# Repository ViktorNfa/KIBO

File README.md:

# KIBO Robot

## Overview

KIBO is an advanced robotics platform designed for modularity and versatility. The project includes hardware designs, electronics, and firmware to control a multi-legged wheeled robotic system. The primary goal is to implement inverse kinematics (IK) walking modes and wheeled modes and gait optimization using Model Predictive Path Integral (MPPI) control through micro-ROS (uROS) in ESP32 and ROS2 nodes with C++.

## Table of Contents

1. [Getting Started](#getting-started)
2. [Features](#features)
3. [Hardware Overview](#hardware-overview)
   - [CAD Files](#cad-files)
   - [Electronics](#electronics)
4. [Software Overview](#software-overview)
   - [ESP32 Firmware](#esp32-firmware)
   - [ROS2 Nodes](#ros2-nodes)
   - [Gait Optimization with MPPI](#gait-optimization-with-mppi)
5. [Installation and Setup](#installation-and-setup)
6. [Usage](#usage)
7. [Contributing](#contributing)
8. [License](#license)
9. [Acknowledgments](#acknowledgments)

## Getting Started

This project is intended for researchers, hobbyists, and developers interested in robotics. To get started with KIBO:

1. Clone this repository.
2. Set up the hardware following the instructions in the [Hardware Overview](#hardware-overview) section.
3. Flash the ESP32 with the firmware provided in the [ESP32 Firmware](#esp32-firmware) section.
4. Configure and run the ROS2 nodes as described in the [ROS2 Nodes](#ros2-nodes) section.

## Features

- **Inverse Kinematics (IK) Walking Modes**: Implement various walking gaits using IK.
- **Gait Optimization**: Optimize the robot's gait using Model Predictive Path Integral (MPPI) control.
- **Micro-ROS (uROS) Integration**: Utilize uROS for real-time communication between ESP32 and ROS2 nodes.
- **ESP32-based Control**: Leverage the ESP32 microcontroller for low-level control and sensor integration.

## Hardware Overview

### CAD Files

The `CAD` directory contains the STL files required to 3D print the robot's structural components. These include parts like the body frame, limbs, and armor:

- **Body Frame**: `Kibo frame.stl`, `Frame End Tip.stl`,`L298N Driver Spacer.stl`
- **Coxa Components**: `Coxa Left.stl`, `Coxa Right.stl`
- **Femur Components**:`Femur Right.stl`,`Femur Left.stl`
- **Tibia Components**: `Tibia.stl`, `Tibia Slider.stl`
- **Armor**: `Bottom Body Armor Left.stl`, `Bottom Body Armor Right.stl`, `Body Armor Spoiler.stl`, `Top Body Armor.stl`
- **Miscellaneous**: `Servo Back Plate.stl`, `Servo Bushing.stl`, `ring.stl`, `Battery holder.stl`

These components can be printed using any standard 3D printer. Ensure that you use durable materials like PLA+ or PETG for better structural integrity.

### Electronics

The `Electronics` directory contains the KiCad files for the KIBO V1 PCB, including:

- **Schematic**: `KIBO V1.kicad_sch`
- **PCB Layout**: `KIBO V1.kicad_pcb`
- **Manufacturing Files**: `KIBO_PCBFab.zip`

You can manufacture the PCB using the provided Gerber files or modify the design using KiCad.

#### Symbols and Footprints

This subdirectory includes additional component libraries for symbols and footprints used in the PCB design:

- ESP32-CAM
- GY-521 (IMU Sensor)
- HC-SR04 (Ultrasonic Sensor)

## Software Overview

### ESP32 Firmware

The ESP32 firmware is still to be developed, but test files can be located in the `Firmware/esp32_tests` directory for the ESP32 and the `Firmware/esp32_cam_tests` directory for the ESP32-CAM. This firmware is responsible for:

- Starting FreeRTOS and seting up the tasks and priorities.
- Managing sensors and actuators.
- Communicating with ROS2 nodes via micro-ROS (uROS).

#### Key Files:

- `platformio.ini`: Configuration file for PlatformIO.
- `src/main.cpp`: Main entry point for the ESP32 application.
- `include/camera_pins.h`: Header files, e.g., defining the camera's GPIO pins.

### ROS2 Nodes

The ROS2 nodes are designed to handle higher-level control and coordination. These nodes communicate with the ESP32 using uROS and handle tasks such as:

- High-level motion planning.
- Real-time data processing from the robot's sensors.
- Gait optimization using MPPI.

#### Planned Features:

The following planned features will be added to the `Simulation` directory.

- **Inverse Kinematics (IK) Implementation**: Calculate joint angles for desired end-effector positions.
- **Gait Optimization with MPPI**: Optimize walking gaits to enhance stability and energy efficiency.

### Gait Optimization with MPPI

MPPI (Model Predictive Path Integral) control is a powerful method for optimizing the robot's gait. It will be used to predict and adjust the robot's movements in real-time, ensuring smooth and stable walking patterns.

## Installation and Setup

### Prerequisites

- **PlatformIO**: Required for building and flashing the ESP32 firmware.
- **ROS2 Humble**: Recommended version of ROS2 for running the ROS2 nodes.
- **uROS Agent**: Necessary for communication between ESP32 and ROS2.

### Instructions

1. **ESP32 Firmware**:
   - Navigate to the `Firmware/esp32_tests` directory.
   - Install the necessary PlatformIO dependencies.
   - Build and upload the firmware to your ESP32 module.

2. **ROS2 Nodes**:
   - Set up a ROS2 workspace and clone this repository into the `src` directory.
   - Build the workspace using `colcon build`.
   - Launch the nodes using the provided launch files.

## Usage

1. Power on the KIBO robot.
2. Launch the ROS2 nodes on your PC.
3. The ESP32 will automatically start communicating with the ROS2 nodes.
4. Use the provided ROS2 interfaces to command the robot and monitor its state.

## Contributing

We welcome contributions to the KIBO project! If you have suggestions, bug reports, or want to contribute new features, please open an issue or submit a pull request.

### Guidelines

- Follow the existing coding style.
- Document your code thoroughly.
- Test your contributions before submitting.

## License

This project is licensed under the MIT License - see the [LICENSE](LICENSE) file for details.

## Acknowledgments

We would like to thank the open-source community for their valuable tools and libraries that made this project possible.

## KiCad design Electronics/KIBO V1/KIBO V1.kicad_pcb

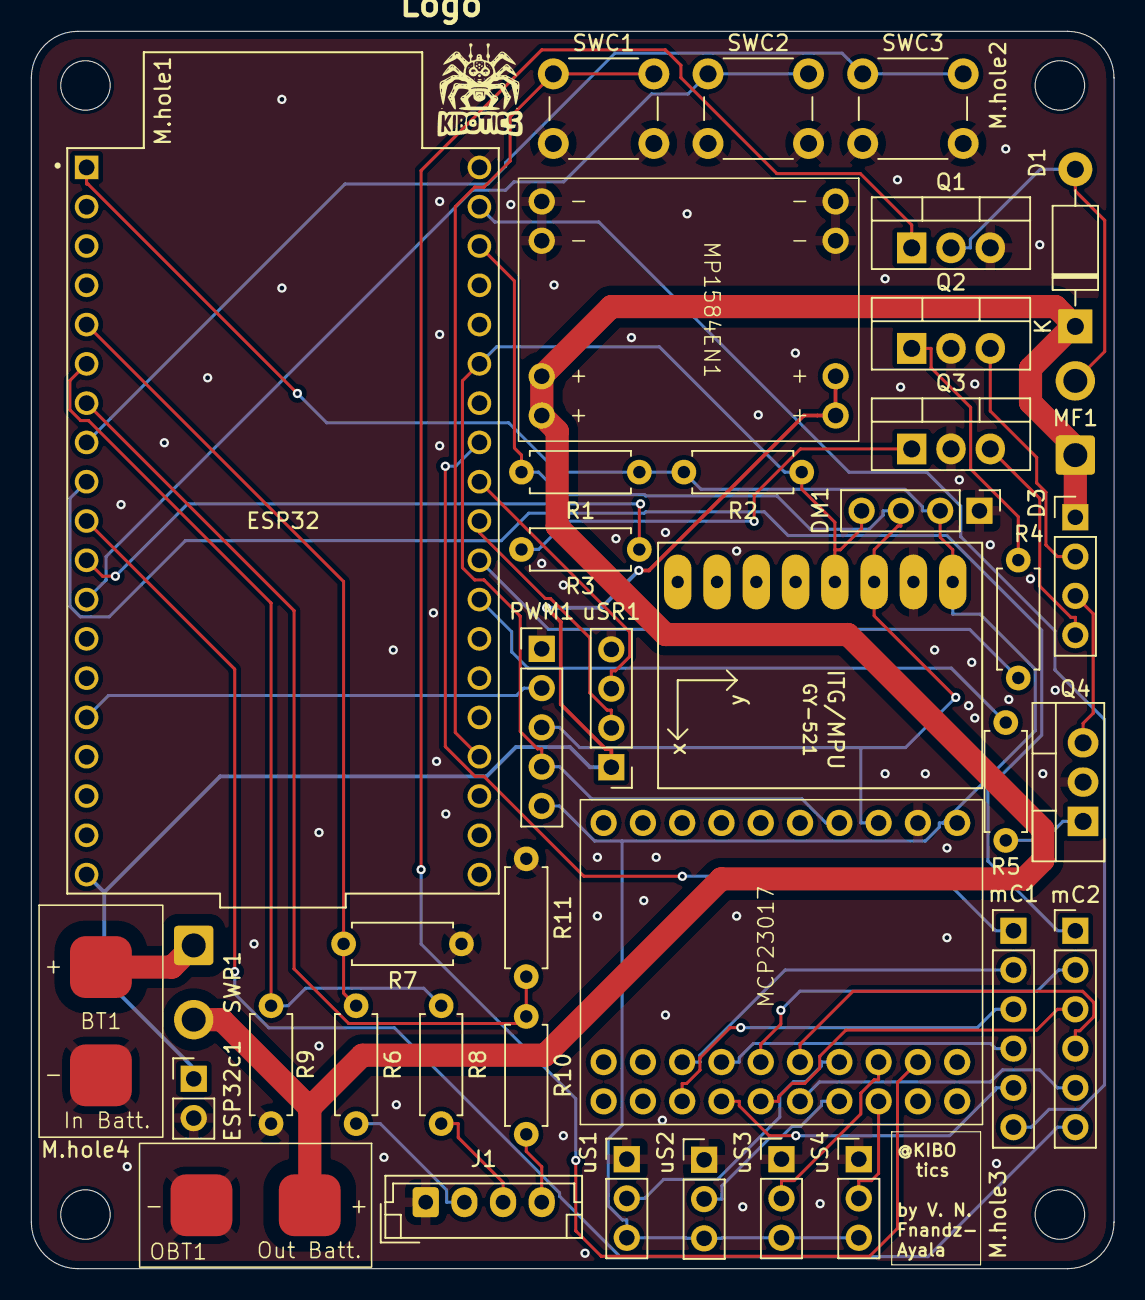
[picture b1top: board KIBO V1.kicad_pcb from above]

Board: 2 copper layers, 70.0 x 80.0 mm, 44 parts (0 on the bottom side), 46 nets.

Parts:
BT1: 11V1; 2xBatterty_Wire_Pads
D1: 1N4001; D_DO-41_SOD81_P10.16mm_Horizontal
D3: LED_AGRB; PinHeader_1x04_P2.54mm_Vertical
DM1: DM-OLED; PinHeader_1x04_P2.54mm_Vertical
ESP32: ESP32-DEVKITC; MODULE_ESP32-DEVKITC
ESP32c1: ESP32-CAM; PinHeader_1x02_P2.54mm_Vertical
GY-521: GY-521
J1: Conn_01x04; JST_EH_B4B-EH-A_1x04_P2.50mm_Vertical
Logo: LOGO
M.hole1, M.hole2, M.hole3, M.hole4: MountingHole_3.2mm_M3
MCP23017: PortExt; MCP23017
MF1: Fan; SolderWire-0.75sqmm_1x02_P4.8mm_D1.25mm_OD2.3mm
MP1584EN1: VoltConv; MP-1584EN
OBT1: UBEC; 2xBatterty_Wire_Pads
PWM1: PWM; PinHeader_1x05_P2.54mm_Vertical
Q1, Q2, Q3, Q4: TIP120; TO-220-3_Vertical
R1, R2: 4k7; R_Axial_DIN0207_L6.3mm_D2.5mm_P7.62mm_Horizontal
R3, R4, R5, R8: 1k; R_Axial_DIN0207_L6.3mm_D2.5mm_P7.62mm_Horizontal
R6, R10: 5k6; R_Axial_DIN0207_L6.3mm_D2.5mm_P7.62mm_Horizontal
R7: 22k; R_Axial_DIN0207_L6.3mm_D2.5mm_P7.62mm_Horizontal
R9: 680; R_Axial_DIN0207_L6.3mm_D2.5mm_P7.62mm_Horizontal
R11: 2k; R_Axial_DIN0207_L6.3mm_D2.5mm_P7.62mm_Horizontal
SWC1, SWC2, SWC3: SW_Push; SW_PUSH_6mm
SWP1: SWP; SolderWire-0.75sqmm_1x02_P4.8mm_D1.25mm_OD2.3mm
mC1, mC2: MotorDriver; PinHeader_1x06_P2.54mm_Vertical
uS1, uS2, uS3, uS4: uSwitch; PinHeader_1x03_P2.54mm_Vertical
uSR1: HC-SR04; PinHeader_1x04_P2.54mm_Vertical

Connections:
+3V3: DM1.2 (VCC_IN), ESP32.1 (3V3), GY-521.VCC, MCP23017.10 (VCC), PWM1.5 (VCC), R1.1, R2.1, uS1.3 (NO), uS2.3 (NO), uS3.3 (NO), uS4.3 (NO)
+5V: ESP32.19 (EXT_5V), ESP32c1.1 (5V), MP1584EN1.7 (OUT+), MP1584EN1.8 (OUT+), uSR1.1 (VCC)
+11V1: D1.1 (K), D3.1 (A), MF1.1 (+), MP1584EN1.3 (IN+), MP1584EN1.4 (IN+), OBT1.1 (IN+), SWP1.2 (B)
/B: ESP32.11 (IO27), R3.1
/CLL1: ESP32.5 (IO34), R6.1, R7.2
/CLL2: ESP32.6 (IO35), R8.1, R9.2
/CLL3: ESP32.7 (IO32), R10.1, R11.2
/ECHO: ESP32.30 (IO18), uSR1.3 (ECHO)
/FAN: MCP23017.27 (B6), Q1.1 (B)
/G: ESP32.28 (IO17), R4.1
/M1EN: ESP32.31 (IO19), mC1.1 (ENA)
/M1IN1: MCP23017.15 (B0), mC1.2 (IN1)
/M1IN2: MCP23017.16 (A0), mC1.3 (IN2)
/M2EN: ESP32.37 (IO23), mC1.6 (ENB)
/M2IN1: MCP23017.17 (B1), mC1.4 (IN3)
/M2IN2: MCP23017.18 (A1), mC1.5 (IN4)
/M3EN: ESP32.9 (IO25), mC2.1 (ENA)
/M3IN1: MCP23017.19 (B2), mC2.2 (IN1)
/M3IN2: MCP23017.20 (A2), mC2.3 (IN2)
/M4EN: ESP32.10 (IO26), mC2.6 (ENB)
/M4IN1: MCP23017.21 (B3), mC2.4 (IN3)
/M4IN2: MCP23017.22 (A3), mC2.5 (IN4)
/OE: ESP32.15 (IO13), PWM1.2 (OE)
/R: ESP32.27 (IO16), R5.1
/S1: MCP23017.23 (B4), uS1.2 (COM)
/S2: MCP23017.24 (A4), uS2.2 (COM)
/S3: MCP23017.25 (B5), uS3.2 (COM)
/S4: MCP23017.26 (A5), uS4.2 (COM)
/SCL: DM1.3 (SCL), ESP32.36 (IO22), GY-521.SCL, MCP23017.8 (SCK), PWM1.3 (SCL), R1.2
/SDA: DM1.4 (SDA), ESP32.33 (IO21), GY-521.SDA, MCP23017.7 (SDA), PWM1.4 (SDA), R2.2
/SW1: ESP32.23 (IO15), SWC1.1
/SW2: ESP32.12 (IO14), SWC2.1
/SW3: ESP32.8 (IO33), SWC3.1
/TRIG: ESP32.29 (IO5), uSR1.2 (TRIG)
GND: BT1.2 (-), DM1.1 (GND), ESP32.38 (GND3), ESP32c1.2 (GND@3), GY-521.GND, J1.1, MCP23017.9 (GND), MP1584EN1.1 (IN-), MP1584EN1.2 (IN-), MP1584EN1.5 (OUT-), MP1584EN1.6 (OUT-), OBT1.2 (IN-), PWM1.1 (GND), Q1.3 (E), Q2.2 (C), Q3.2 (C), Q4.2 (C), R7.1, R9.1, R11.1, SWC1.2, SWC2.2, SWC3.2, uS1.1 (NC), uS2.1 (NC), uS3.1 (NC), uS4.1 (NC), uSR1.4 (GND)
unnamed: BT1.1 (+), SWP1.1 (A)
unnamed: D1.2 (A), MF1.2 (-), Q1.2 (C)
unnamed: D3.4 (BK), Q3.3 (E)
unnamed: D3.2 (GK), Q2.3 (E)
unnamed: D3.3 (RK), Q4.3 (E)
unnamed: J1.2, R6.2
unnamed: J1.3, R8.2
unnamed: J1.4, R10.2
unnamed: Q2.1 (B), R4.2
unnamed: Q3.1 (B), R3.2
unnamed: Q4.1 (B), R5.2

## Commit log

2024-03-26 Uploaded current schematics
2024-03-26 Cleaned up schematics
    In order to upload them again with a corrected gitignore
2024-03-26 Updated .gitignore for KiCAD
2024-03-26 Re-uploaded KiCAD schematics and libraries
2024-03-26 Create LICENSE
2024-04-04 feat: added code folder with esp32 electronics tests
2024-04-05 feat: added tests for mcp23017 and limit switch
2024-04-06 feat: added RGB LEDs and ESP32-CAM with PIR to schematic
2024-04-06 feat: added tests for the L298N DC motor controller
2024-04-06 feat: deleted .vscode folder to clean with .gitignore
2024-04-06 fix: added vscode files to gitignore
2024-04-06 fix: re-added extensions and settings json
2024-04-10 feat: Uploaded Tibia Assembly V3
2024-04-18 feat: testing discord webhook
2024-04-19 feat: Uploaded Tibia Assembly V5.f3d
    Uploaded the latest version with stetical improvements, and better attachment of the servo.
2024-04-19 feat: Uploaded Tibia Assembly
    Added TPU elements to cushion impacts, modified the tibia structure to fit said part
2024-04-22 feat: Uploaded Tibia Assembly.f3d
    Fixed sliding joint problems, added spacers for the servo back plate, M3 nuts, bolts and washers
2024-04-25 feat: Added femur to Tibia Assembly
    Added new femur
2024-04-25 feat: added tests for fan and RBG led control
2024-04-26 feat: added ESP32-CAM tests
2024-05-29 feat: added openCV object detection code
2024-05-30 feat: added working PIR & SD card tests
2024-06-09 feat: corrected schematics, finished all footprints and checked ERC
2024-06-12 feat: created PCB power pins for ESP32cam and added battery measurement script
2024-06-12 feat: added buttons test
2024-06-17 feat: Started working on the frame
2024-06-18 feat: added internal temp and hc-sr04 esp32cam test
2024-06-18 feat: added push buttons, batt measu and hc-sr04 esp32cam to schematic and footprints
2024-06-20 feat: setup PCB size, holes and all U components
2024-06-21 feat: final position of all footprints on PCB
2024-06-22 fix: cleaned footprint placement, text and logos
2024-06-22 feat: finished PCB and its CAD
2024-06-24 feat: added latest tibia assembly and stl files for printable parts
    Fixed the pivot holes for the servo back plates (9,2 mm diameter) and discarded the parts named Ring, added a temporary m3 hole in the tibia as a slide stopper
2024-06-26 fix: added polarity sign to battery pads
2024-06-27 feat: Created the Kibo Assembly.f3d file
    Created the Kibo Assembly.f3d file as substitution of the file Kibo v9.f3d, which im not deleting in case victor messes up the github again.
2024-06-27 fix: we only store .stl and .step files, .f3d files under request to Alvi
2024-06-28 fix: deleted all old stl files
    Deletes all the older stl files due to the bad orientation of the parts
2024-06-28 feat: Uploaded the fixed stl files
    As per Victor´s request the STLs have been fixed, hopefully he enjoys them.
2024-07-02 feat: added calibration parts stls
2024-07-03 feat: added gerber files
2024-07-03 fix: Modified coxa, femur and tibia slider
    Uploaded the modified versions of said parts, the slider gets a slightly bigger hole, the femur and coxa get smaller holes for the servo horn´s screws, going from 1.5 to 1.4 mm
2024-07-19 fix: Corrected al the parts as Viktor requested
    Went back to the first Serbo back plate and ring set up from the chipo github, the corrections mentioned include: tibia slider hole enlargement (sus), tibia support less design, servo back plate hole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
2024-07-20 Fix: ServoBackPlate thickness fix
    reduced thicknes of the backplate at the top to leave a safe amount of space, and reduced thickness at the bottom so that it works as intended and it touches the servo
2024-08-03 feat: Uploaded final stl versions, mirror stls included
2024-08-09 Fix: Delted incorrect femur stl´s
2024-08-09 Feat: Added remaining final parts
2024-08-30 Added logo
2024-08-30 Update LICENSE
2024-09-04 feat: created the URDF Models folder and uploaded URDF V1
2024-09-05 fix: deleted old frame and armor stlf files and mirror files
    Frame and armor files will be updated, mirror files will no longer be used as they are not needed, the user can mirror the stl files inside Cura or any other slider programs.
2024-09-05 feat: uploaded final versions of body armor a driver spacers
    Final fixxes for the Body Armor top and bottom, the driver spacer lenght got also corrected and a purely cosmeticall part for the body armor is included(Body Armor Spoiler)
2024-09-05 fix: reorganized directories
2024-09-05 fix: update README.md
2024-09-05 feat: updated the Readme.md files
2024-09-05 fix: selected a better logo.png photo
    No more robot dick pics pls
2024-09-05 fix:new logo
    new mfkn logo
